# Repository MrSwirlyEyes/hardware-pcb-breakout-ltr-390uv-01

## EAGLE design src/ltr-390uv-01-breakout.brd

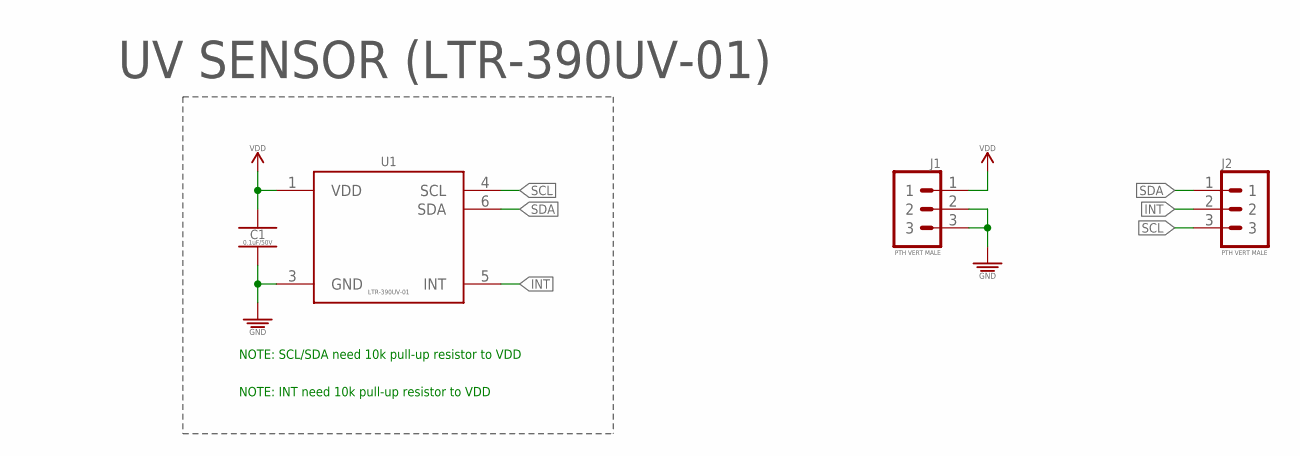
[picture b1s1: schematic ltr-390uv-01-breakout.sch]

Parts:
C1: 0.1uF/50V; CAPC1005X55_SMD-0402
J1, J2: PTH VERT MALE; HDRV3W64P254_1X3_762X254X838B
U1: LTR-390UV-01; SON65P200X200X70-6N-LTR-390UV-01

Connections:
GND: C1.2, J1.2, J1.3, U1.3 (GND)
INT: J2.2, U1.5 (INT)
SCL: J2.3, U1.4 (SCL)
SDA: J2.1, U1.6 (SDA)
VDD: C1.1, J1.1, U1.1 (VDD)

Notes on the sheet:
UV SENSOR (LTR-390UV-01)
NOTE: SCL/SDA need 10k pull-up resistor to VDD
NOTE: INT need 10k pull-up resistor to VDD

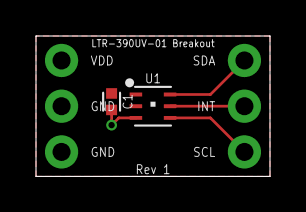
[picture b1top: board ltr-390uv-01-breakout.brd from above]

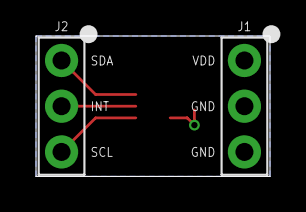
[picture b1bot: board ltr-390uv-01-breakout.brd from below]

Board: 2 copper layers, 13.0 x 7.8 mm, 4 parts (2 on the bottom side), 5 nets.

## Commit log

2021-08-11 Initialize repo.
